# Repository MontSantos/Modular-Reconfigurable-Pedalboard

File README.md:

# Modular Reconfigurable Pedalboard
A modular, reconfigurable guitar/bass pedalboard designed as a **universal base** for **interchangeable effect modules**.  
Current version includes two analog effect circuits: an **MXR-style Distortion+ inspired clone** and a **silicon Fuzz Face–inspired fuzz**.

---

---

## Features (current)

- A modular board capable of hosting **two 8 pin effect modules** simultaneously
- Two analog effect modules included:
  - **MXR-style distortion** (Distortion+/D+ family inspiration)
  - **Silicon Fuzz Face–inspired fuzz**
- Each module supports **up to two PCB-mounted potentiometers** for onboard control (e.g., Gain/Level, Fuzz/Volume)
- Designed for common use with string instruments, such as **electric guitars** or **basses**
- Fully **customizable** and **open-source** for public access

---

## Repository structure

- `Imagens cartuchos/` - Presents the cover images and logos used to decorate the cartridges
- `PlacaGeral/` — The **main board** (the “placão”): carrier/backplane PCB that hosts the modules and concentrates the shared wiring.
- `Pedais/` — The **effect modules** (schematics/PCB files for Dizzy and Amorphous, and future modules).
- `Modelos pedal/` — Mechanical assets (e.g., templates, outlines, 3D/visual models, and design references).
- `fotos pedal/` — Build photos and progress shots used in the README and documentation.
  
---

## Included effect modules

### 1) **Dizzy** - Silicon Fuzz Face–inspired fuzz 

A two-transistor silicon fuzz, implemented with a **negative-ground** power scheme for easy integration with other pedal models.
Great for raw, dirty and aggressive tones.

This module is nicknamed **Dizzy**, referencing the fuzz’s naturally **psychedelic, dizzy aesthetic**.

Reference / inspiration:
- Fuzz Central (Fuzz Face): https://fuzzcentral.ssguitar.com/fuzzface.php

### 2) **Amorphous** - MXR-style distortion (Distortion+ inspired)

A classic op-amp gain stage with germanium diode clipping (the “raw” distortion character).  
Useful for gritty tones.  

This module is nicknamed **Amorphous**, referencing how distortion/clipping turns a clean waveform into a denser, less-defined shape.

Reference / inspiration:
- Electrosmash analysis: https://www.electrosmash.com/mxr-distortion-plus-analysis

## The **Main Board**

The **PlacaGeral** is the carrier PCB that turns this project into a modular system. In practice, it works like a small “backplane” for pedals:

- Provides **two module slots** (two 8-pin effect modules at the same time)
- Routes **audio I/O** and keeps a consistent grounding scheme across modules
- Distributes **9V DC power** to the modules (the main board is **center-positive** oriented — double-check before powering)
- Offers a standardized mechanical/electrical base so modules can be swapped without rewiring the whole pedalboard

> ⚠️ Many common pedal supplies are **center-negative**. Do **not** plug a standard center-negative supply into a center-positive board without an adapter/inverter — unless you want to release the magic smoke (and smell something funny).

---

## Cartridge (module holder)

Each effect module is mounted on a removable 3d printed Gameboy inspired **cartridge**, which provides mechanical support and keeps the 8-pin module interface consistent across pedals.

This cartridge was adapted from an existing model available at **(link)** and then modified for this project (fit/clearance/alignment), including:
- alignment tweaks in order to support pedals PCBs.
- clearance changes to avoid collisions with tall components, and parts of the main board structure

Reference / inspiration:
 - [(link)](https://grabcad.com/library/original-gameboy-cartridge)

---

## Power & safety notes

- **Verify supply voltage (9V DC) and polarity** before connecting any power source.
- Before first power-up:
  - Confirm electrolytic/tantalum capacitors orientations.
  - Verify power supply polarity: the main board is **center-positive** oriented.
 
## 3D printed structures notes

It was necessary to modify the case of the **Main board** to accommodate the final board layout. The front piece of the case was cut so the potentiometers could fit in the case. The removed piece was then put back in place once the circuit board was in position.
 
## Electronics hardware notes

During initial bring-up, the main board required a small routing correction: 
 - To properly route the **effect IN/OUT** of each module, it is necessary **cut two traces per pedal** (one affecting the input path and one affecting the output path).  
 - To fix the audio routing, the board was **rewired** (trace cuts + jumper wires) for each module’s input and output.
 - Additionally, the two buffers were removed because they were not handling the signal swing correctly and ended up clipping the **negative half-cycle** of the waveform. This change restored a more symmetric signal path.
This was a quick rework step applied on the assembled board and will be addressed in the next PCB revision.

## Credits / Contributions

- **João Neto** — Pedal testing and validation **before** assembling the PCBs (pre print tests).
- **Guilherme Santos** — Pedal testing and validation **before** assembling the PCBs (pre print tests); **PCB design**, **assembly**, and **final testing** of the system.
- **Romulo Soli** — **3D modeling** (enclosure/mechanical models).
- **Yanis** -

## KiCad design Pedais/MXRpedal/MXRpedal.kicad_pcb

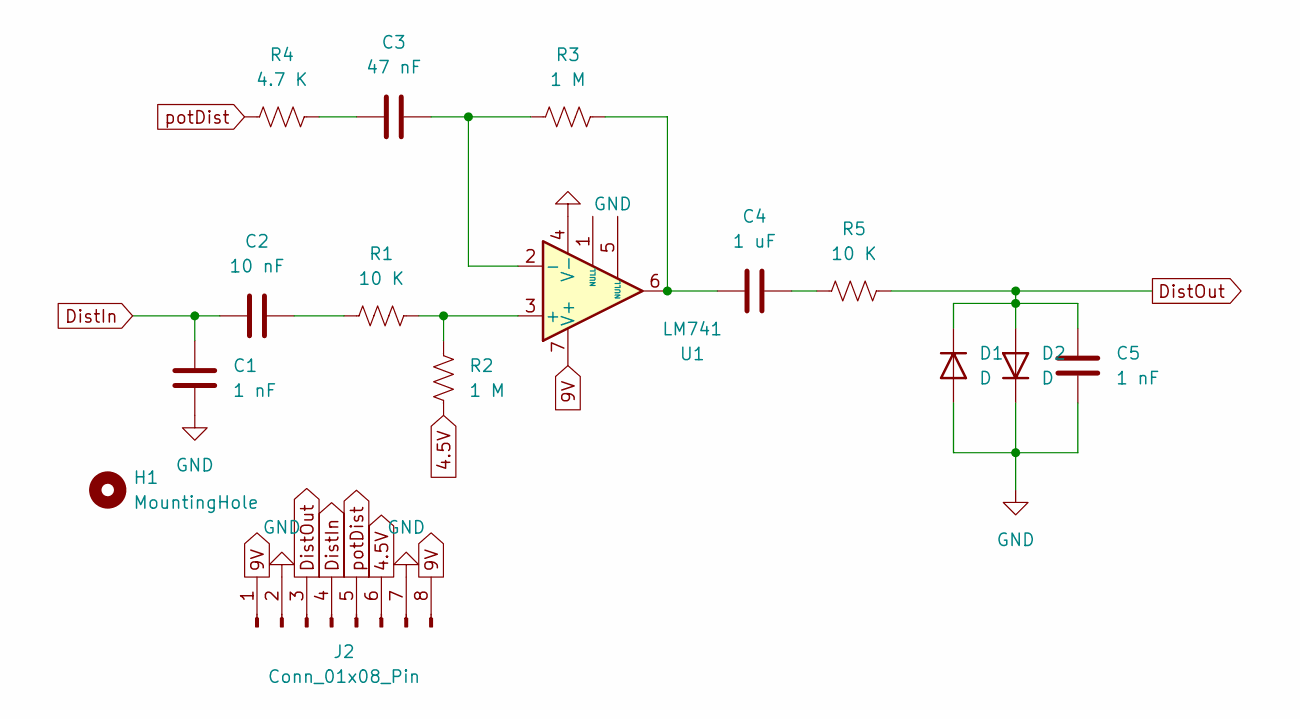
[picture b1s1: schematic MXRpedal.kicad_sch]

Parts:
C1, C5: 1 nF; C_0805_2012Metric
C2: 10 nF; C_0805_2012Metric
C3: 47 nF; C_1206_3216Metric
C4: 1 uF; C_0805_2012Metric
D1, D2: D; D_A-405_P7.62mm_Horizontal
H1: MountingHole; MountingHole_3.5mm
J2: Conn_01x08_Pin; PinHeader_1x08_P2.00mm_Horizontal
R1, R5: 10 K; R_1206_3216Metric
R2, R3: 1 M; R_1206_3216Metric
R4: 4.7 K; R_1206_3216Metric
U1: LM741; SOIC-8_3.9x4.9mm_P1.27mm

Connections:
4.5V: J2.6, R2.1
9V: J2.1, J2.8, U1.7 (V+)
DistIn: C1.1, C2.1, J2.4
DistOut: C5.2, D1.1 (K), D2.2 (A), J2.3, R5.2
GND: C1.2, C5.1, D1.2 (A), D2.1 (K), J2.2, J2.7, U1.4 (V-)
unnamed: C2.2, R1.1
unnamed: C3.1, R4.2
unnamed: C4.1, R3.2, U1.6
unnamed: C4.2, R5.1
unnamed: R1.2, R2.2, U1.3 (+)
unnamed: C3.2, R3.1, U1.2 (-)
potDist: J2.5, R4.1

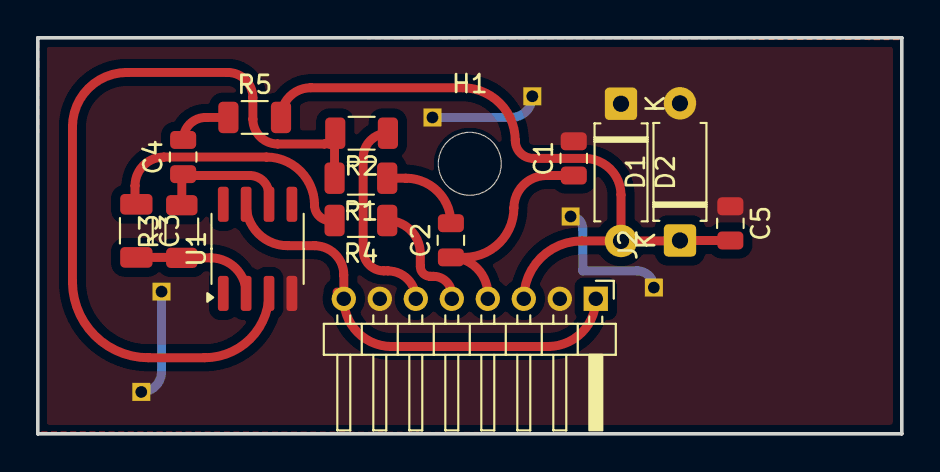
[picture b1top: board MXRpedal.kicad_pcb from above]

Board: 2 copper layers, 48.0 x 22.0 mm, 15 parts (0 on the bottom side), 12 nets.

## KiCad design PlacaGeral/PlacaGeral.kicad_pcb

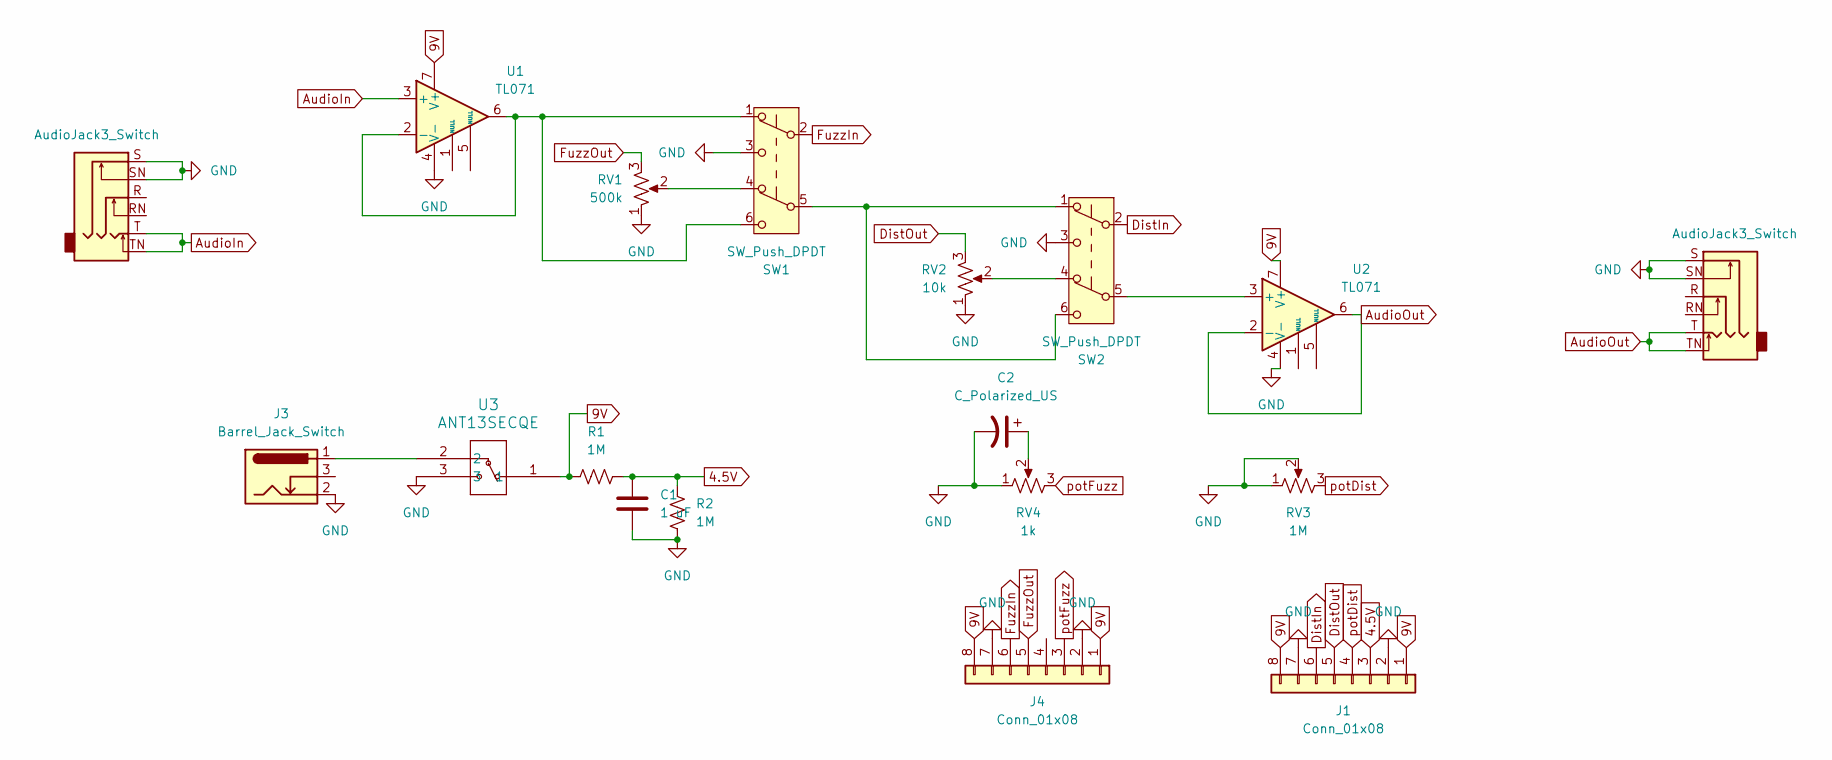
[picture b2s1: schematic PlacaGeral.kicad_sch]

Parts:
C1: 1 uF; C_0805_2012Metric
C2: C_Polarized_US; CP_EIA-3528-21_Kemet-B
J1, J4: Conn_01x08; PinHeader_1x08_P2.00mm_Vertical
J2, J6: AudioJack3_Switch; PJ-644C
J3: Barrel_Jack_Switch; BarrelJack_GCT_DCJ200-10-A_Horizontal
R1, R2: 1M; R_1206_3216Metric
RV1: 500k; Potentiometer_Piher_PC-16_Single_Horizontal
RV2: 10k; Potentiometer_Piher_PC-16_Single_Horizontal
RV3: 1M; Potentiometer_Piher_PC-16_Single_Horizontal
RV4: 1k; Potentiometer_Piher_PC-16_Single_Horizontal
SW1, SW2: SW_Push_DPDT; pbs24202p
U1, U2: TL071; SOIC-8_3.9x4.9mm_P1.27mm
U3: ANT13SECQE; ANT13SEC_CRS

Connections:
4.5V: C1.1, J1.3, R1.2, R2.2
9V: J1.1, J1.8, J4.1, J4.8, R1.1, U1.7 (V+), U2.7 (V+), U3.1
AudioIn: J6.T, J6.TN, U1.3 (+)
AudioOut: J2.T, J2.TN, U2.2 (-), U2.6
DistIn: J1.6, SW2.2 (B)
DistOut: J1.5, RV2.3
FuzzIn: J4.6, SW1.2 (B)
FuzzOut: J4.5, RV1.3
GND: C1.2, C2.2, J1.2, J1.7, J2.S, J2.SN, J3.2, J4.2, J4.7, J6.S, J6.SN, R2.1, RV1.1, RV2.1, RV3.1, RV3.2, RV4.1, SW1.3 (C), SW2.3 (C), U1.4 (V-), U2.4 (V-), U3.3
unnamed: C2.1, RV4.2
unnamed: J3.1, U3.2
unnamed: RV1.2, SW1.4 (A)
unnamed: RV2.2, SW2.4 (A)
unnamed: SW1.5 (B), SW2.1 (A), SW2.6 (C)
unnamed: SW1.1 (A), SW1.6 (C), U1.2 (-), U1.6
unnamed: SW2.5 (B), U2.3 (+)
potDist: J1.4, RV3.3
potFuzz: J4.3, RV4.3

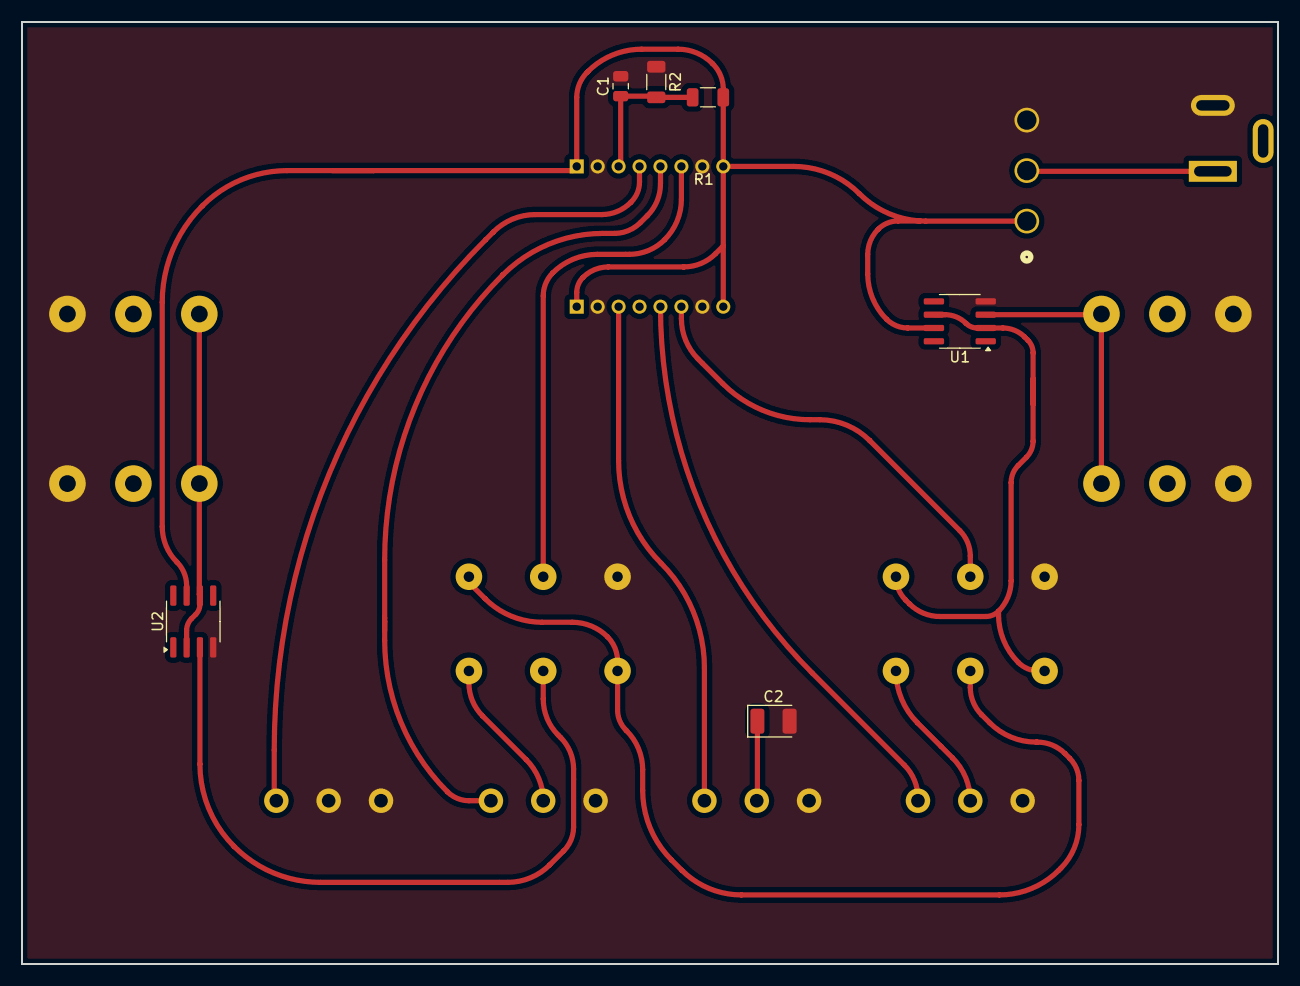
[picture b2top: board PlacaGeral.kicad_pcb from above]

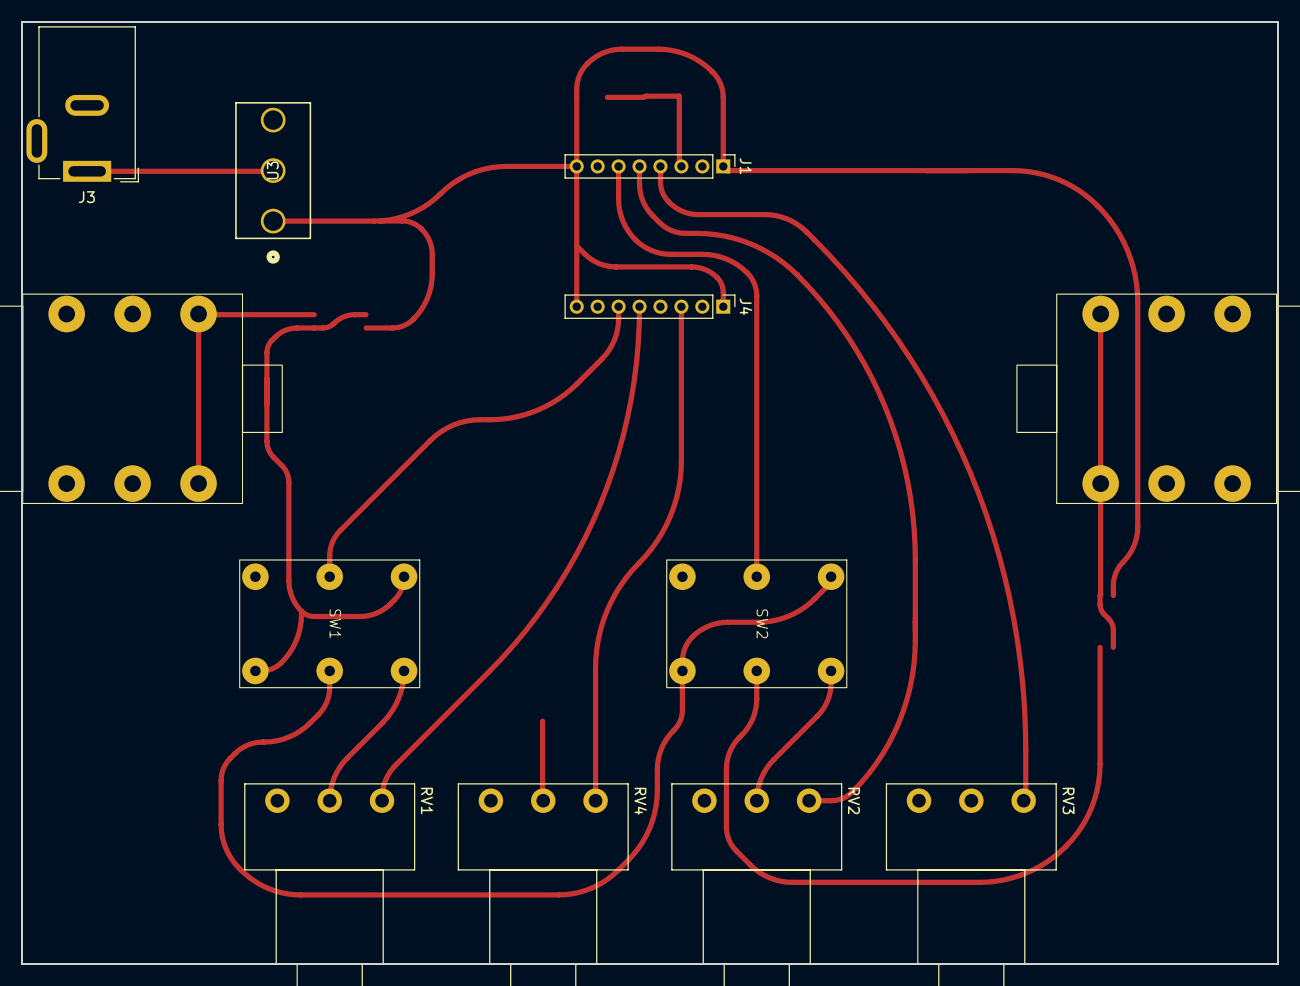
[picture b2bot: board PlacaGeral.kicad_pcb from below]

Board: 2 copper layers, 120.0 x 90.0 mm, 18 parts (12 on the bottom side), 18 nets.

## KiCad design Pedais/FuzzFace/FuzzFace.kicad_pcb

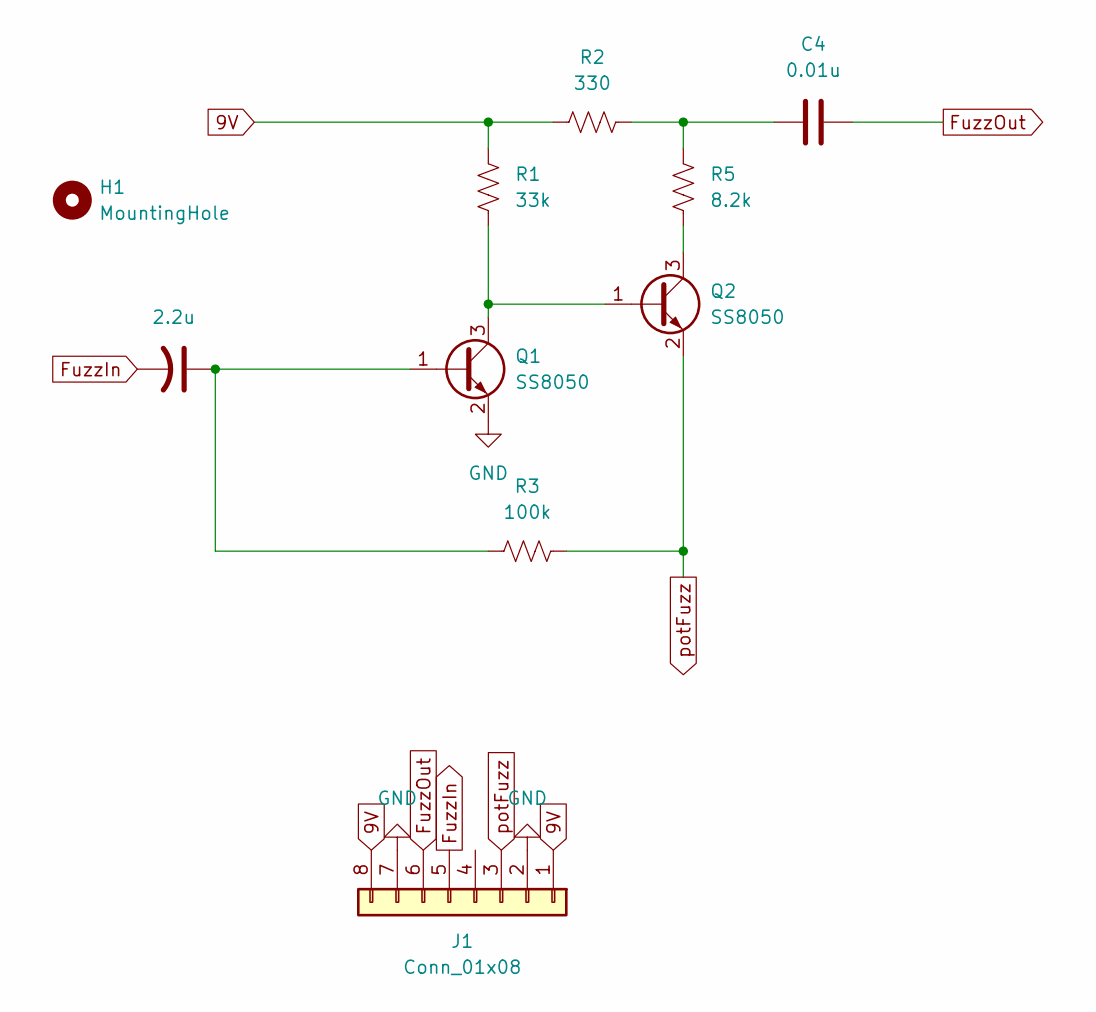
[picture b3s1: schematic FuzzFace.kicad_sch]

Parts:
C3: 2.2u; CP_EIA-3528-21_Kemet-B_HandSolder
C4: 0.01u; C_Axial_L3.8mm_D2.6mm_P7.50mm_Horizontal
H1: MountingHole; MountingHole_3.5mm
J1: Conn_01x08; PinHeader_1x08_P2.00mm_Horizontal
Q1, Q2: SS8050; SOT-23
R1: 33k; R_0805_2012Metric
R2: 330; R_0805_2012Metric
R3: 100k; R_1206_3216Metric
R5: 8.2k; R_0805_2012Metric

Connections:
9V: J1.1, J1.8, R1.2, R2.1
FuzzIn: C3.2, J1.5
FuzzOut: C4.2, J1.6
GND: J1.2, J1.7, Q1.2 (E)
unnamed: C4.1, R2.2, R5.2
unnamed: C3.1, Q1.1 (B), R3.1
unnamed: Q1.3 (C), Q2.1 (B), R1.1
unnamed: Q2.3 (C), R5.1
potFuzz: J1.3, Q2.2 (E), R3.2

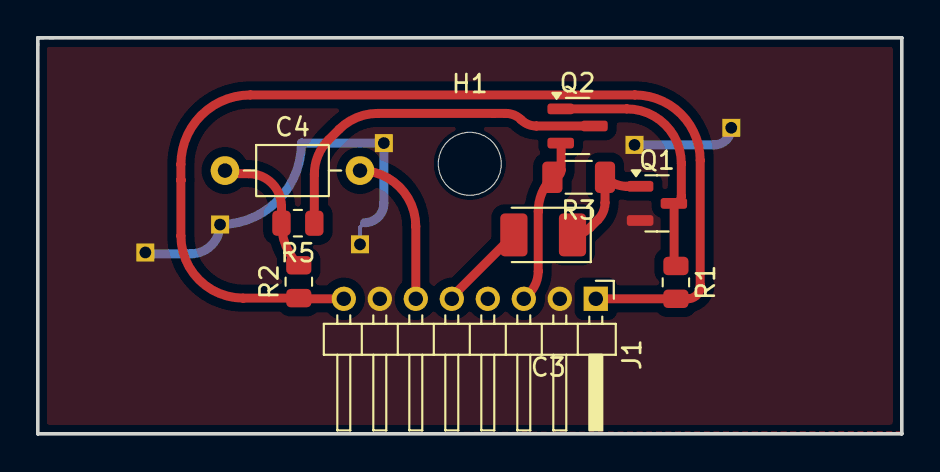
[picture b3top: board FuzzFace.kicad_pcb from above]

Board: 2 copper layers, 48.0 x 22.0 mm, 10 parts (0 on the bottom side), 9 nets.

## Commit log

2025-12-12 Cha cha cha changeeeees
